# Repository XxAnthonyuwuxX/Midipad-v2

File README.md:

# Midipad-v2
Midipad, started as a project for blueprint program, this midipad will help you find note tones more quickly, as well as experiment with notes and much more, using a DAW—preferably FL Studio.

here is a view of the pcb plate

here is a view of the 3d case model with and without the pcb

here is a view of the schematic

and this is the list of materials u will need to build this (BOM)
12x Cherry MX Switches
12x DSA Keycaps
1x Encoder Knob
6x M3x5x4 Heatset Inserts
6x M3x16mm Screws
12x 1N4148 DO-35 Diodes
12x SK6812 MINI-E LEDs
1x 0.91 inch 128x32 OLED Display I2C
1x EC11 Rotary Encoder
1x XIAO RP2040
1x Case (3 printed parts)

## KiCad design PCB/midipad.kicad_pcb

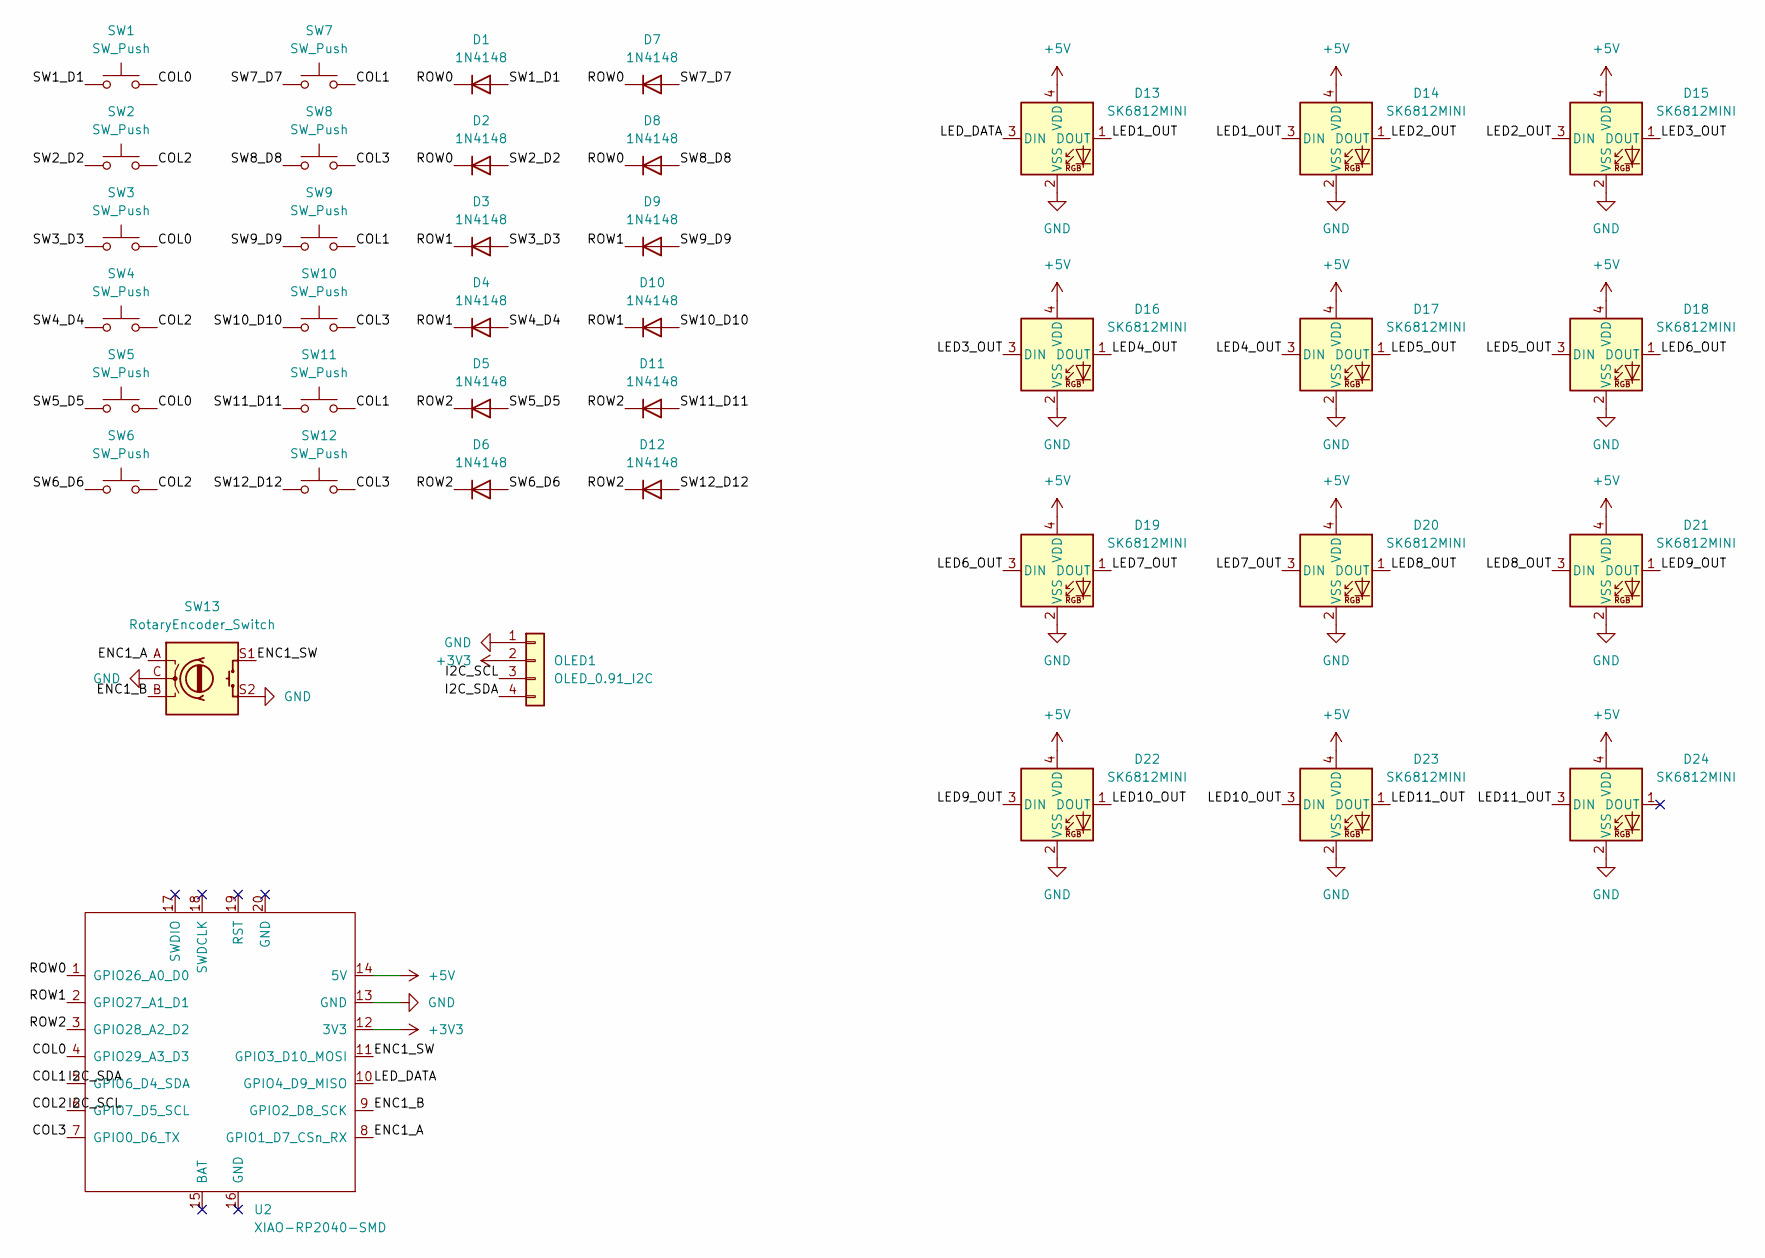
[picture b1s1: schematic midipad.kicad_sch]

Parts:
D1, D2, D3, D4, D5, D6, D7, D8, D9, D10, D11, D12: 1N4148; D_DO-35_SOD27_P7.62mm_Horizontal
D13, D14, D15, D16, D17, D18, D19, D20, D21, D22, D23, D24: SK6812MINI; LED_SK6812MINI_PLCC4_3.5x3.5mm_P1.75mm
OLED1: OLED_0.91_I2C; PinHeader_1x04_P2.54mm_Vertical
SW1, SW2, SW3, SW4, SW5, SW6, SW7, SW8, SW9, SW10, SW11, SW12: SW_Push; SW_Cherry_MX_1.00u_PCB
SW13: RotaryEncoder_Switch; RotaryEncoder_Alps_EC11E-Switch_Vertical_H20mm
U2: XIAO-RP2040-SMD

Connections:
+3V3: OLED1.2, U2.12 (3V3)
+5V: D13.4 (VDD), D14.4 (VDD), D15.4 (VDD), D16.4 (VDD), D17.4 (VDD), D18.4 (VDD), D19.4 (VDD), D20.4 (VDD), D21.4 (VDD), D22.4 (VDD), D23.4 (VDD), D24.4 (VDD), U2.14 (5V)
/COL0: SW1.2, SW3.2, SW5.2, U2.4 (GPIO29_A3_D3)
/COL1: OLED1.4, SW7.2, SW9.2, SW11.2, U2.5 (GPIO6_D4_SDA)
/COL2: OLED1.3, SW2.2, SW4.2, SW6.2, U2.6 (GPIO7_D5_SCL)
/COL3: SW8.2, SW10.2, SW12.2, U2.7 (GPIO0_D6_TX)
/ENC1_A: SW13.A, U2.8 (GPIO1_D7_CSn_RX)
/ENC1_B: SW13.B, U2.9 (GPIO2_D8_SCK)
/ENC1_SW: SW13.S1, U2.11 (GPIO3_D10_MOSI)
/LED1_OUT: D13.1 (DOUT), D14.3 (DIN)
/LED2_OUT: D14.1 (DOUT), D15.3 (DIN)
/LED3_OUT: D15.1 (DOUT), D16.3 (DIN)
/LED4_OUT: D16.1 (DOUT), D17.3 (DIN)
/LED5_OUT: D17.1 (DOUT), D18.3 (DIN)
/LED6_OUT: D18.1 (DOUT), D19.3 (DIN)
/LED7_OUT: D19.1 (DOUT), D20.3 (DIN)
/LED8_OUT: D20.1 (DOUT), D21.3 (DIN)
/LED9_OUT: D21.1 (DOUT), D22.3 (DIN)
/LED10_OUT: D22.1 (DOUT), D23.3 (DIN)
/LED11_OUT: D23.1 (DOUT), D24.3 (DIN)
/LED_DATA: D13.3 (DIN), U2.10 (GPIO4_D9_MISO)
/ROW0: D1.1 (K), D2.1 (K), D7.1 (K), D8.1 (K), U2.1 (GPIO26_A0_D0)
/ROW1: D3.1 (K), D4.1 (K), D9.1 (K), D10.1 (K), U2.2 (GPIO27_A1_D1)
/ROW2: D5.1 (K), D6.1 (K), D11.1 (K), D12.1 (K), U2.3 (GPIO28_A2_D2)
/SW1_D1: D1.2 (A), SW1.1
/SW2_D2: D2.2 (A), SW2.1
/SW3_D3: D3.2 (A), SW3.1
/SW4_D4: D4.2 (A), SW4.1
/SW5_D5: D5.2 (A), SW5.1
/SW6_D6: D6.2 (A), SW6.1
/SW7_D7: D7.2 (A), SW7.1
/SW8_D8: D8.2 (A), SW8.1
/SW9_D9: D9.2 (A), SW9.1
/SW10_D10: D10.2 (A), SW10.1
/SW11_D11: D11.2 (A), SW11.1
/SW12_D12: D12.2 (A), SW12.1
GND: D13.2 (VSS), D14.2 (VSS), D15.2 (VSS), D16.2 (VSS), D17.2 (VSS), D18.2 (VSS), D19.2 (VSS), D20.2 (VSS), D21.2 (VSS), D22.2 (VSS), D23.2 (VSS), D24.2 (VSS), OLED1.1, SW13.C, SW13.S2, U2.13 (GND)

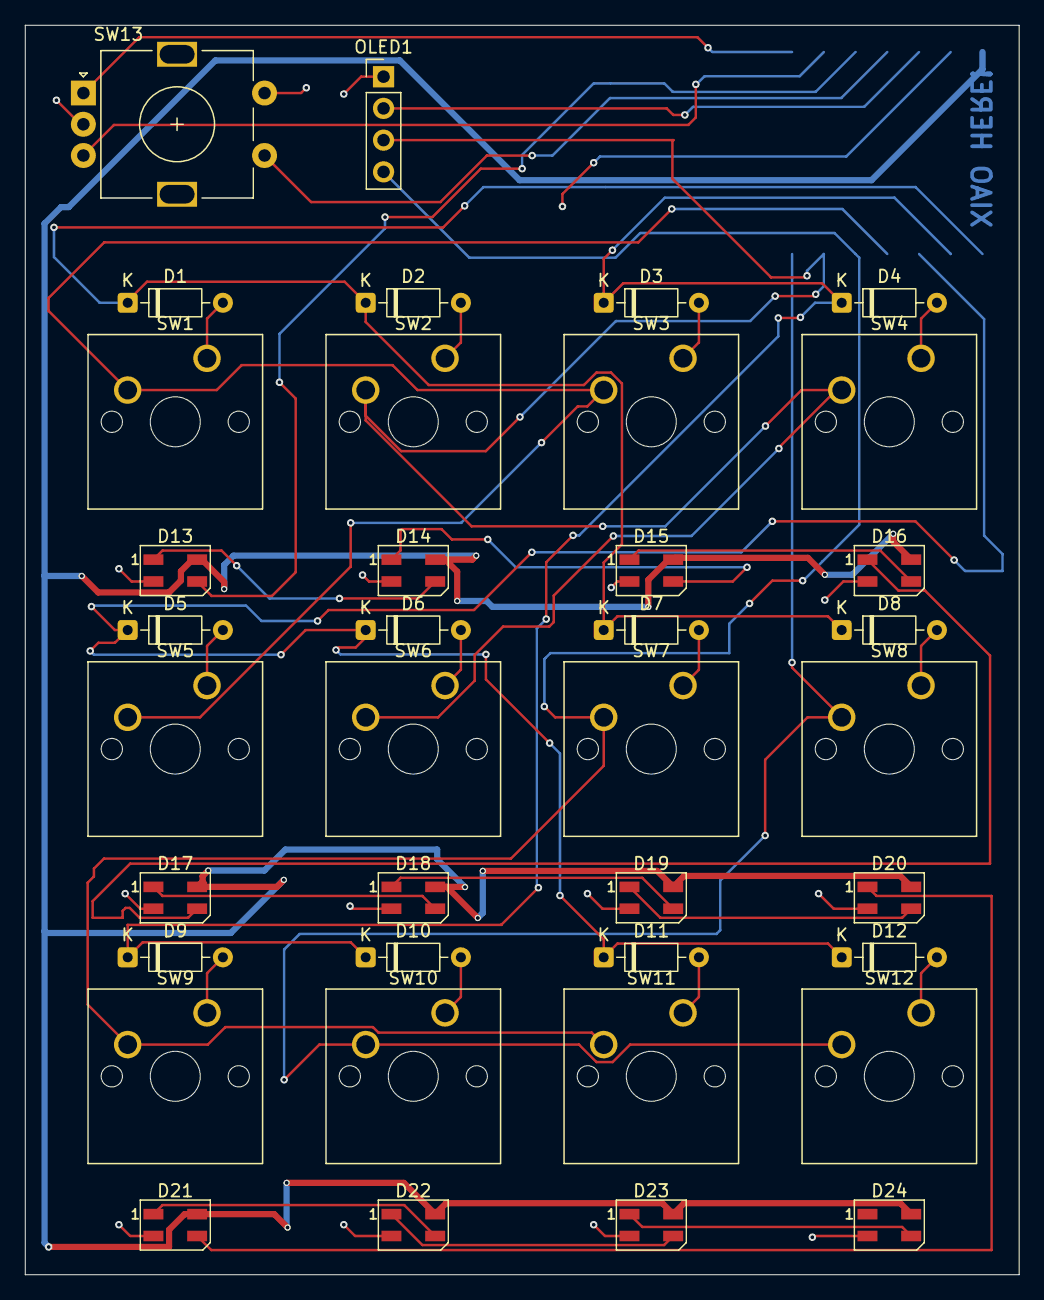
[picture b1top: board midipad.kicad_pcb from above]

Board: 2 copper layers, 79.6 x 100.0 mm, 39 parts (1 on the bottom side), 37 nets.

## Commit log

2026-01-28 Update README with images and BOM details
    Added images of PCB, 3D case model, schematic, and BOM.
2026-01-28 generic commit
2026-02-25 generic2
